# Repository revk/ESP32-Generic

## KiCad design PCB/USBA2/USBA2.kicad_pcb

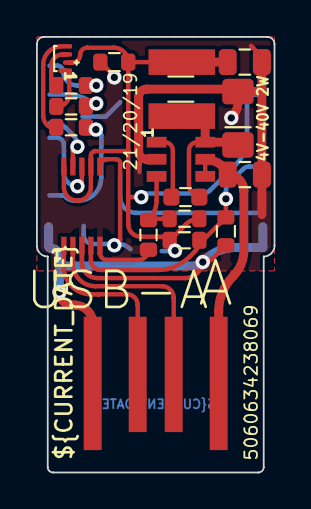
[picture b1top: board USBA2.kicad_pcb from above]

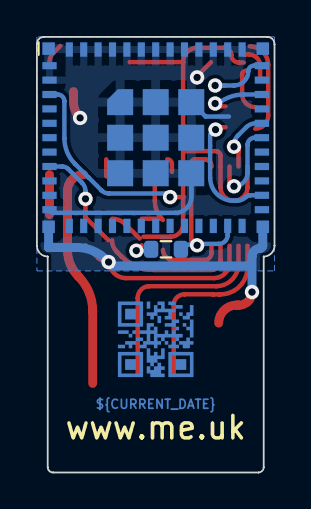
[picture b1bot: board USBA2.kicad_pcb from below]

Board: 2 copper layers, 13.2 x 24.2 mm, 20 parts (3 on the bottom side), 16 nets.

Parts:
C1: 100nF; C_0603_
C2: 2.2uF; C_0805_
C3: 10uF; C_0805_
C4: 100nF; C_0603
C5: 1uF; C_0603
D1: LED_BARG; MHS190RGBCT
D2: Schottky; D_1206_
J1: USB_A; USB-A-PCB
L1: 6.8uH; L_4x4_
R1: 300R; R_0603
R2: 1K; R_0603
R3: 100R; R_0603
R4: 100k 1%; R_0603
R5: 30k 1%; R_0603
R6: 10k; R_0603
R7: 4k7; R_0603
U1: ESP32-PICO-MINI-02
U2: LMR16006YDDCR; SOT-23-Thin-6-Reg
U3: CH340X
U4: QR; QR-GENERIC

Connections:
+3.3V: C4.1, D1.2 (A), R4.1, R6.1, R7.1, U1.3 (3V3), U2.7 (VOUT), U3.7 (VCC), U3.10 (V3)
B: R3.2, U1.33 (IO19)
DC: J1.1 (VBUS), U2.4 (SHDN), U2.5 (VIN)
EN: C5.2, R6.2, U1.8 (EN), U3.4 (~RTS)
G: R2.2, U1.26 (IO20)
GND: C4.2, C5.1, J1.4 (GND), R5.1, U1.1 (GND), U1.2 (GND), U1.11 (GND), U1.14 (GND), U1.36 (GND), U1.37 (GND), U1.38 (GND), U1.39 (GND), U1.40 (GND), U1.41 (GND), U1.42 (GND), U1.43 (GND), U1.44 (GND), U1.45 (GND), U1.46 (GND), U1.47 (GND), U1.48 (GND), U1.49 (GND), U1.50 (GND), U1.51 (GND), U1.52 (GND), U1.53 (GND), U2.2 (GND), U3.3 (GND), U3.5 (~CTS)
GPIO0: R7.2, U1.23 (IO0), U3.6 (TNOW/~DTR)
I: U1.30 (RXD0), U3.8 (TXD)
unnamed: D1.1 (BK), R3.1
unnamed: D1.4 (GK), R2.1
unnamed: D1.3 (RK), R1.1
unnamed: J1.3 (D+), U3.1 (UD+)
unnamed: J1.2 (D-), U3.2 (UD-)
unnamed: R4.2, R5.2, U2.3 (FB)
O: U1.31 (TXD0), U3.9 (RXD)
R: R1.2, U1.35 (IO21)

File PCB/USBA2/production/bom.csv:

Designator,Footprint,Quantity,Value,LCSC Part #
C1,C_0603_,1,100nF,C30926
C2,C_0805_,1,2.2uF,C19110
C3,C_0805_,1,10uF,C17024
C4,C_0603,1,100nF,
C5,C_0603,1,1uF,
D1,MHS190RGBCT,1,LED_BARG,C409798
D2,D_1206_,1,Schottky,C143805
L1,L_4x4_,1,6.8uH,C354575
R1,R_0603,1,300R,
R2,R_0603,1,1K,
R3,R_0603,1,100R,
R4,R_0603,1,100k 1%,C14675
R5,R_0603,1,30k 1%,C100001
R6,R_0603,1,10k,
R7,R_0603,1,4k7,
U1,ESP32-PICO-MINI-02,1,ESP32-PICO-MINI-02,C2980306
U2,SOT-23-Thin-6-Reg,1,LMR16006YDDCR,C290195
U3,CH340X,1,CH340X,C3035748

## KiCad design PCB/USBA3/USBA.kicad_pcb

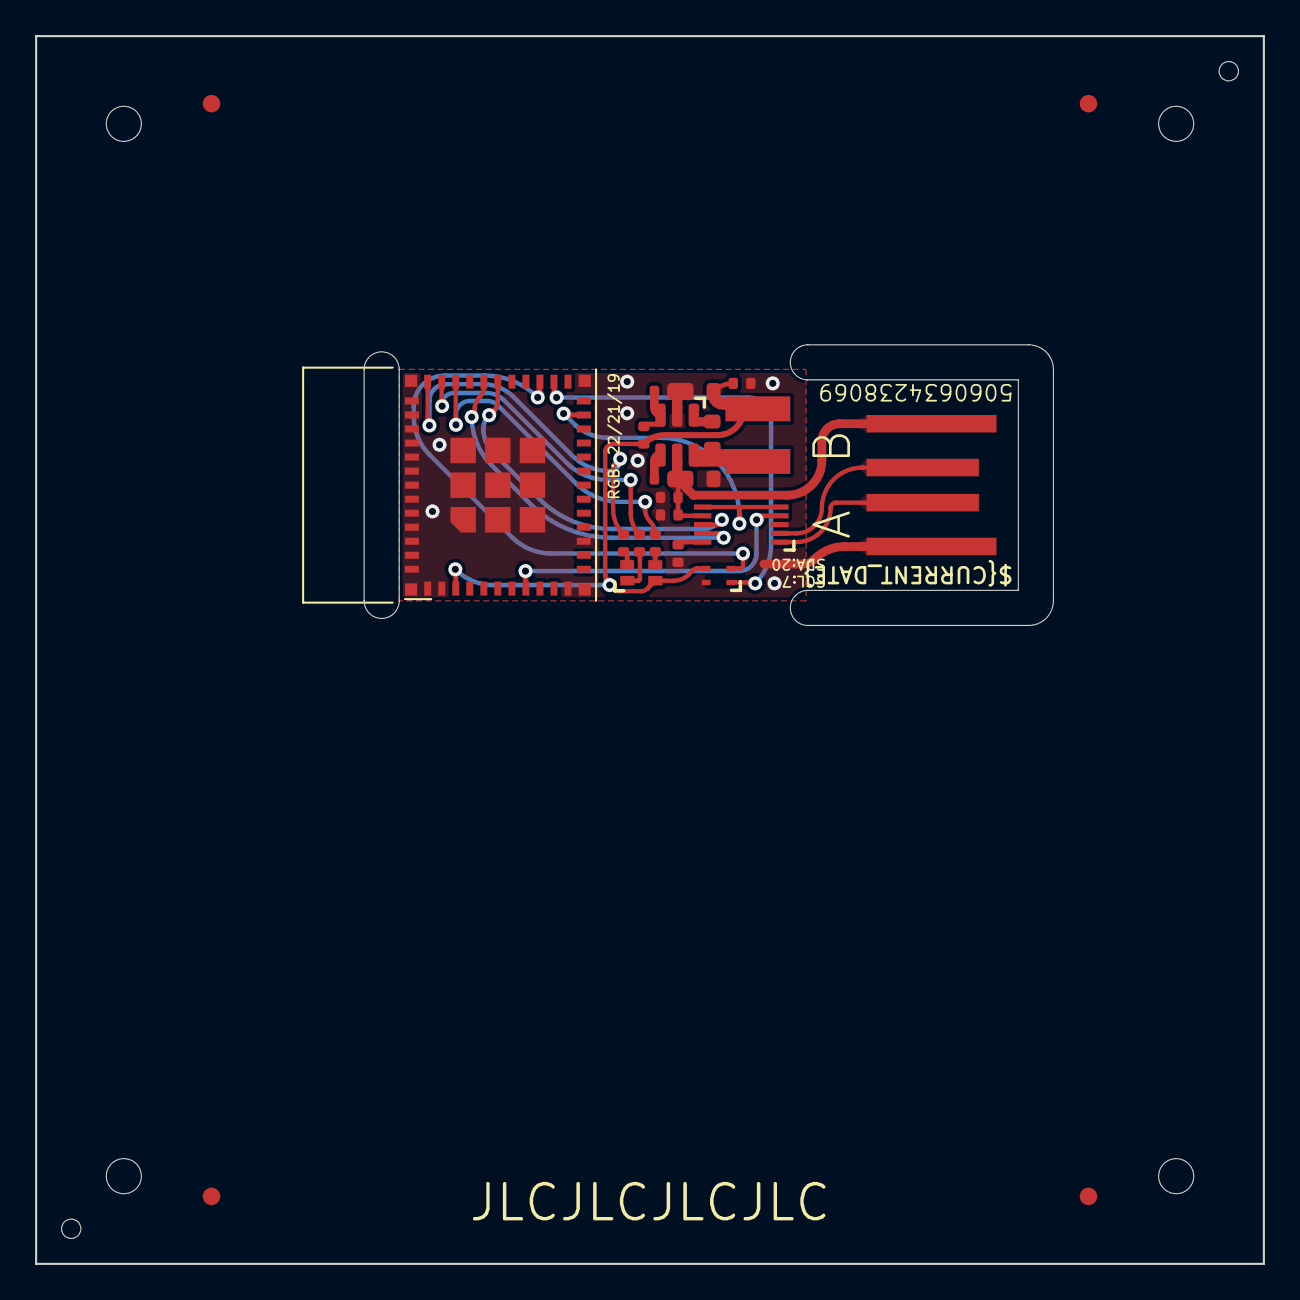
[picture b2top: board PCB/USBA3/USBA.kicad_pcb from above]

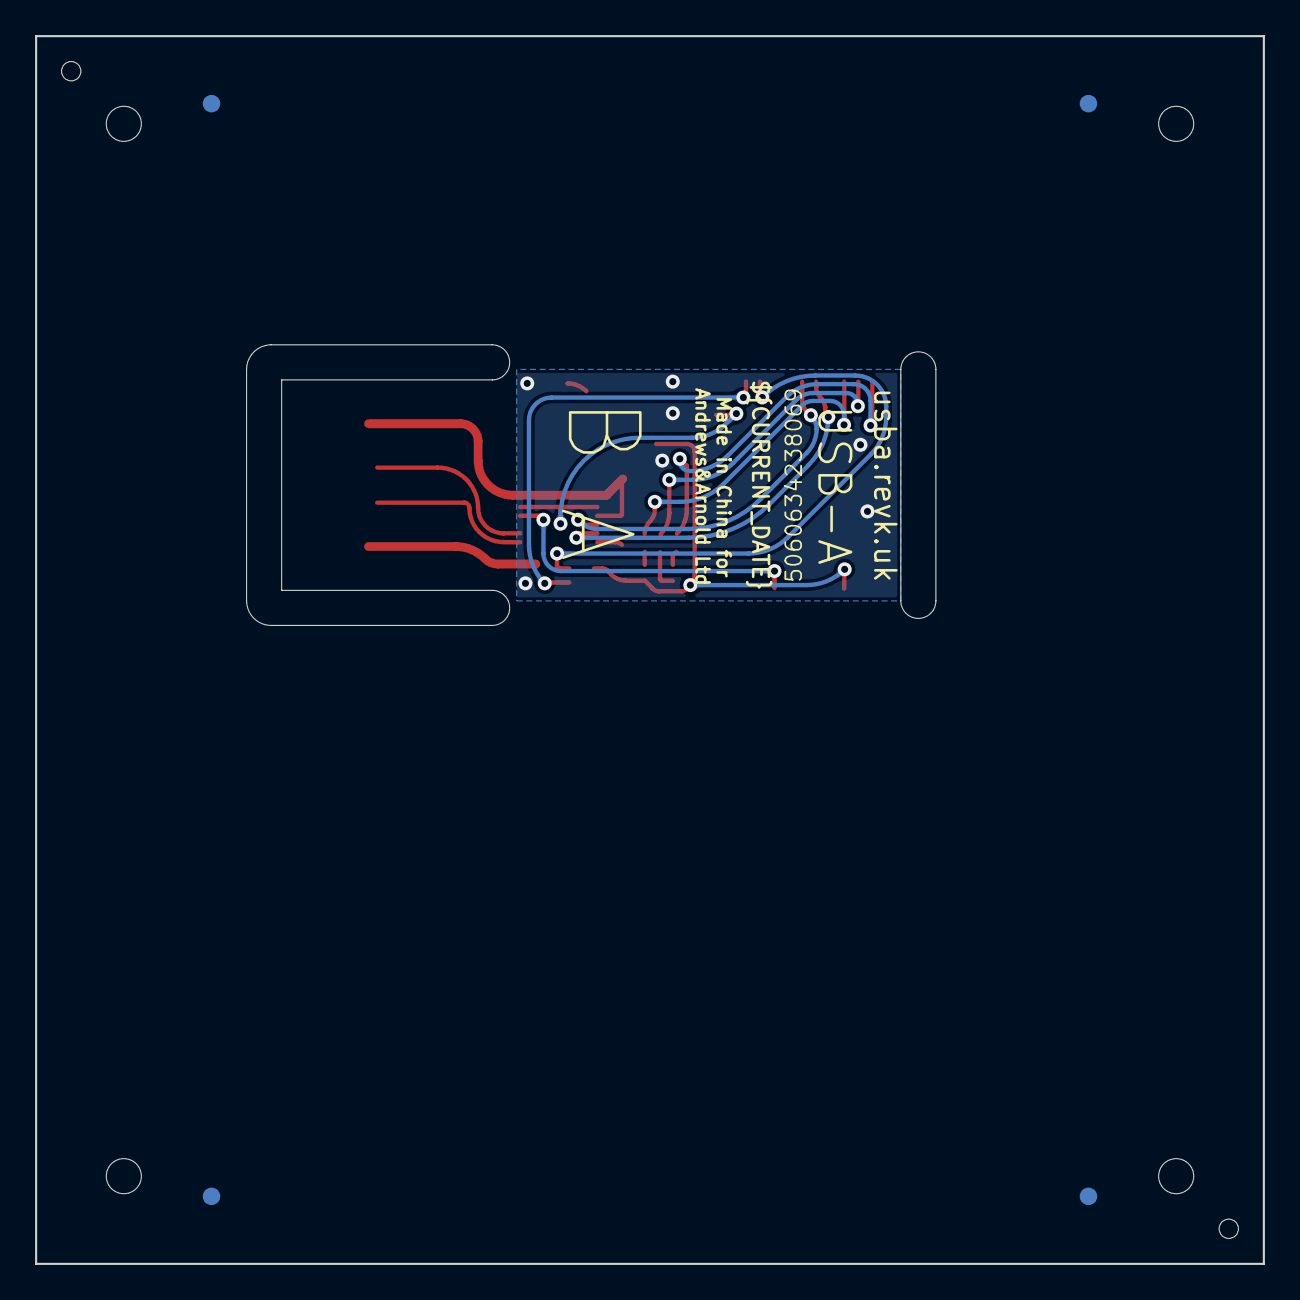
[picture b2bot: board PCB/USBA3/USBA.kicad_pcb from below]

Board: 2 copper layers, 70.0 x 70.0 mm, 23 parts (2 on the bottom side), 18 nets.

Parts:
C1: 22uF; C_0402
C2: 10nF; C_0402
C3, C4: 100nF; C_0402
C6: 10uF 50V; C_0603_
C7: 10uF 6.3V; C_0603_
C8: 100nF; C_0603_
D2: RGB; LED-RGB-1.6x1.6
J1: USB_A; USB-A-PCB
L2: 10uH; L_4x4_
PCB1: 70x70; PCB7070
R4: 680R; R_0402
R5: 2K; R_0402
R7: 220R; R_0402
R9: 124k; R_0402_
R10: 39k2; R_0402_
R11: 1M; R_0402_
U1: ESP32-PICO-MINI-02
U3: CH340X
U5: MD8942; SOT-23-6-MD8942
U6: SHT40; Sensirion_DFN-4_1.5x1.5mm_P0.5mm_SHT4x
V1, V2: 70; VCUT70

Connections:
+3.3V: C4.1, D2.4 (A), U1.3 (3V3), U5.8 (VOUT), U6.3 (VDD)
B: R7.2, U1.33 (IO19)
EN: U1.8 (EN), U3.4 (~RTS)
G: R5.2, U1.35 (IO21)
GND: C1.1, C2.1, C3.1, C4.2, J1.4 (GND), U1.1 (GND), U1.2 (GND), U1.11 (GND), U1.14 (GND), U1.36 (GND), U1.37 (GND), U1.38 (GND), U1.39 (GND), U1.40 (GND), U1.41 (GND), U1.42 (GND), U1.43 (GND), U1.44 (GND), U1.45 (GND), U1.46 (GND), U1.47 (GND), U1.48 (GND), U1.49 (GND), U1.50 (GND), U1.51 (GND), U1.52 (GND), U1.53 (GND), U3.3 (GND), U5.2 (GND), U5.7 (GND), U6.4 (VSS)
GPIO0: U1.23 (IO0), U3.5 (~CTS), U3.6 (TNOW/~DTR)
I: U1.30 (RXD0), U3.8 (TXD)
unnamed: D2.3 (BK), R7.1
unnamed: D2.2 (GK), R5.1
unnamed: D2.1 (RK), R4.1
unnamed: J1.3 (D+), U3.1 (UD+)
unnamed: J1.2 (D-), U3.2 (UD-)
unnamed: C2.2, U3.10 (V3)
O: U1.31 (TXD0), U3.9 (RXD)
R: R4.2, U1.34 (IO22)
SCL: U1.27 (IO7), U6.2 (SCL)
SDA: U1.26 (IO20), U6.1 (SDA)
VBUS: C1.2, C3.2, J1.1 (VBUS), U3.7 (VCC), U5.5 (VIN)

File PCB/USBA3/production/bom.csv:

Designator,Footprint,Quantity,Value,LCSC Part #
C1,C_0402,1,22uF,
C2,C_0402,1,10nF,
"C3, C4",C_0402,2,100nF,
C6,C_0603_,1,10uF 50V,C1591
C7,C_0603_,1,10uF 6.3V,C1691
C8,C_0603_,1,100nF,
D2,LED-RGB-1.6x1.6,1,RGB,C264508
L2,L_4x4_,1,10uH,
R10,R_0402_,1,39k2,
R11,R_0402_,1,1M,
R4,R_0402,1,680R,
R5,R_0402,1,2K,
R7,R_0402,1,220R,
R9,R_0402_,1,124k,
U1,ESP32-PICO-MINI-02,1,ESP32-PICO-MINI-02,C2980306
U3,CH340X,1,CH340X,C3035748
U5,SOT-23-6-MD8942,1,MD8942,C2684786
U6,Sensirion_DFN-4_1.5x1.5mm_P0.5mm_SHT4x,1,SHT40,C2909890

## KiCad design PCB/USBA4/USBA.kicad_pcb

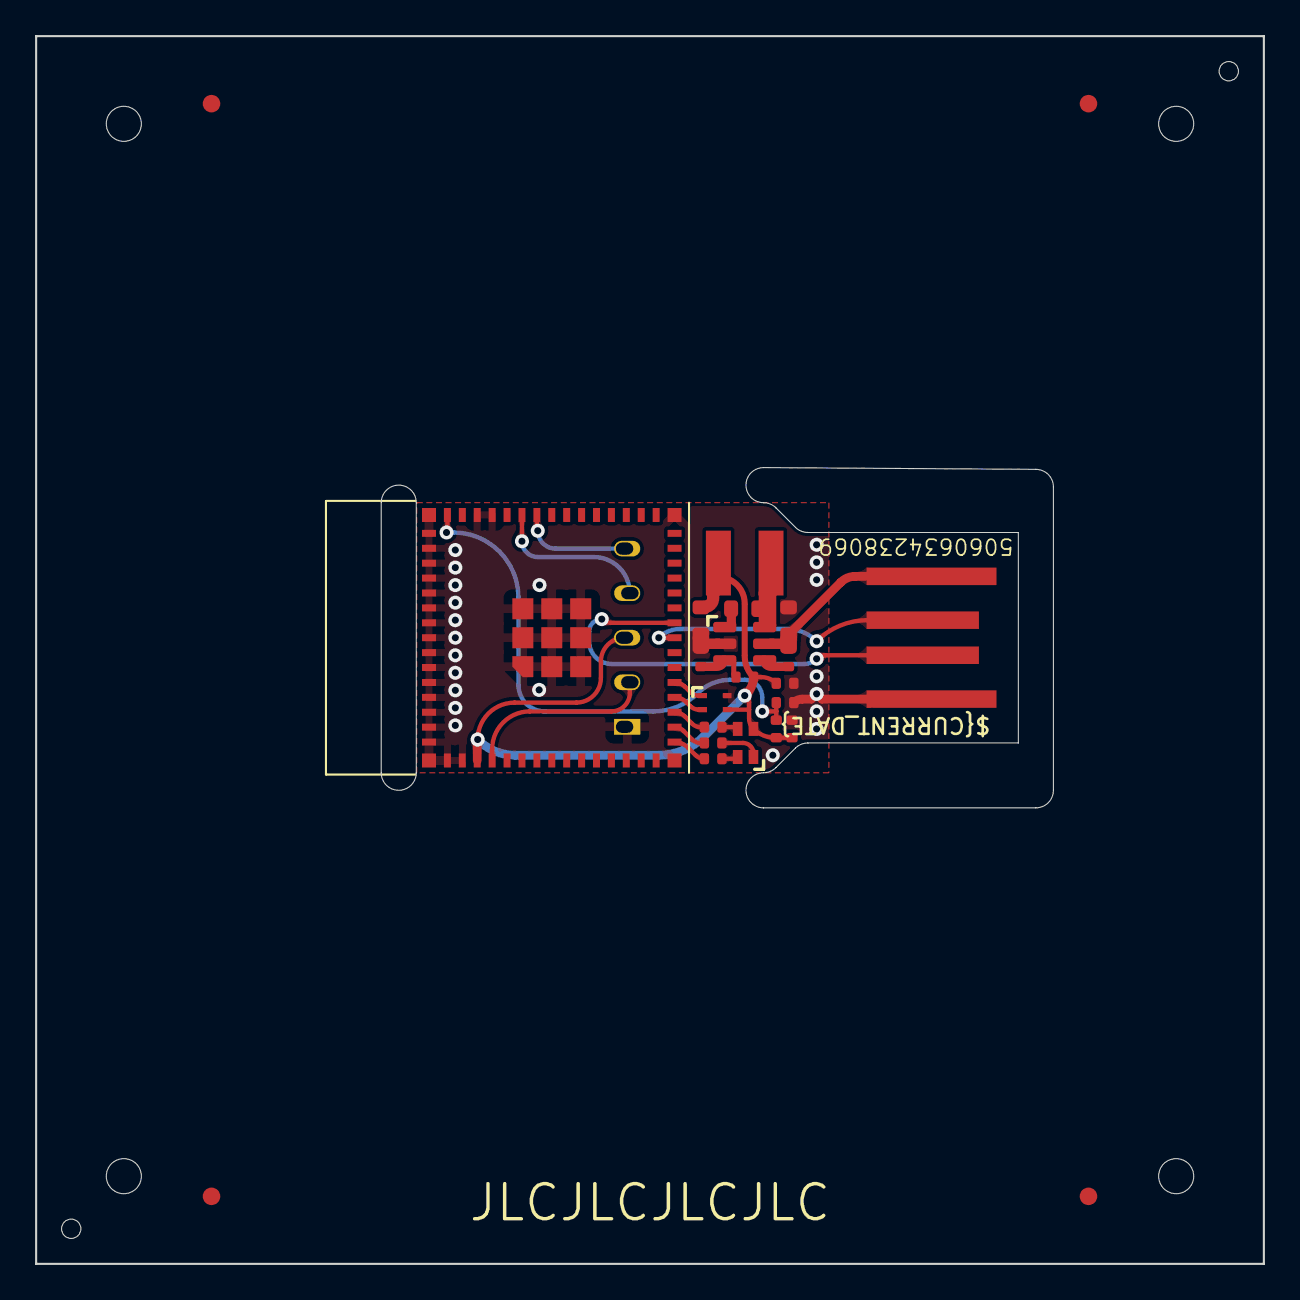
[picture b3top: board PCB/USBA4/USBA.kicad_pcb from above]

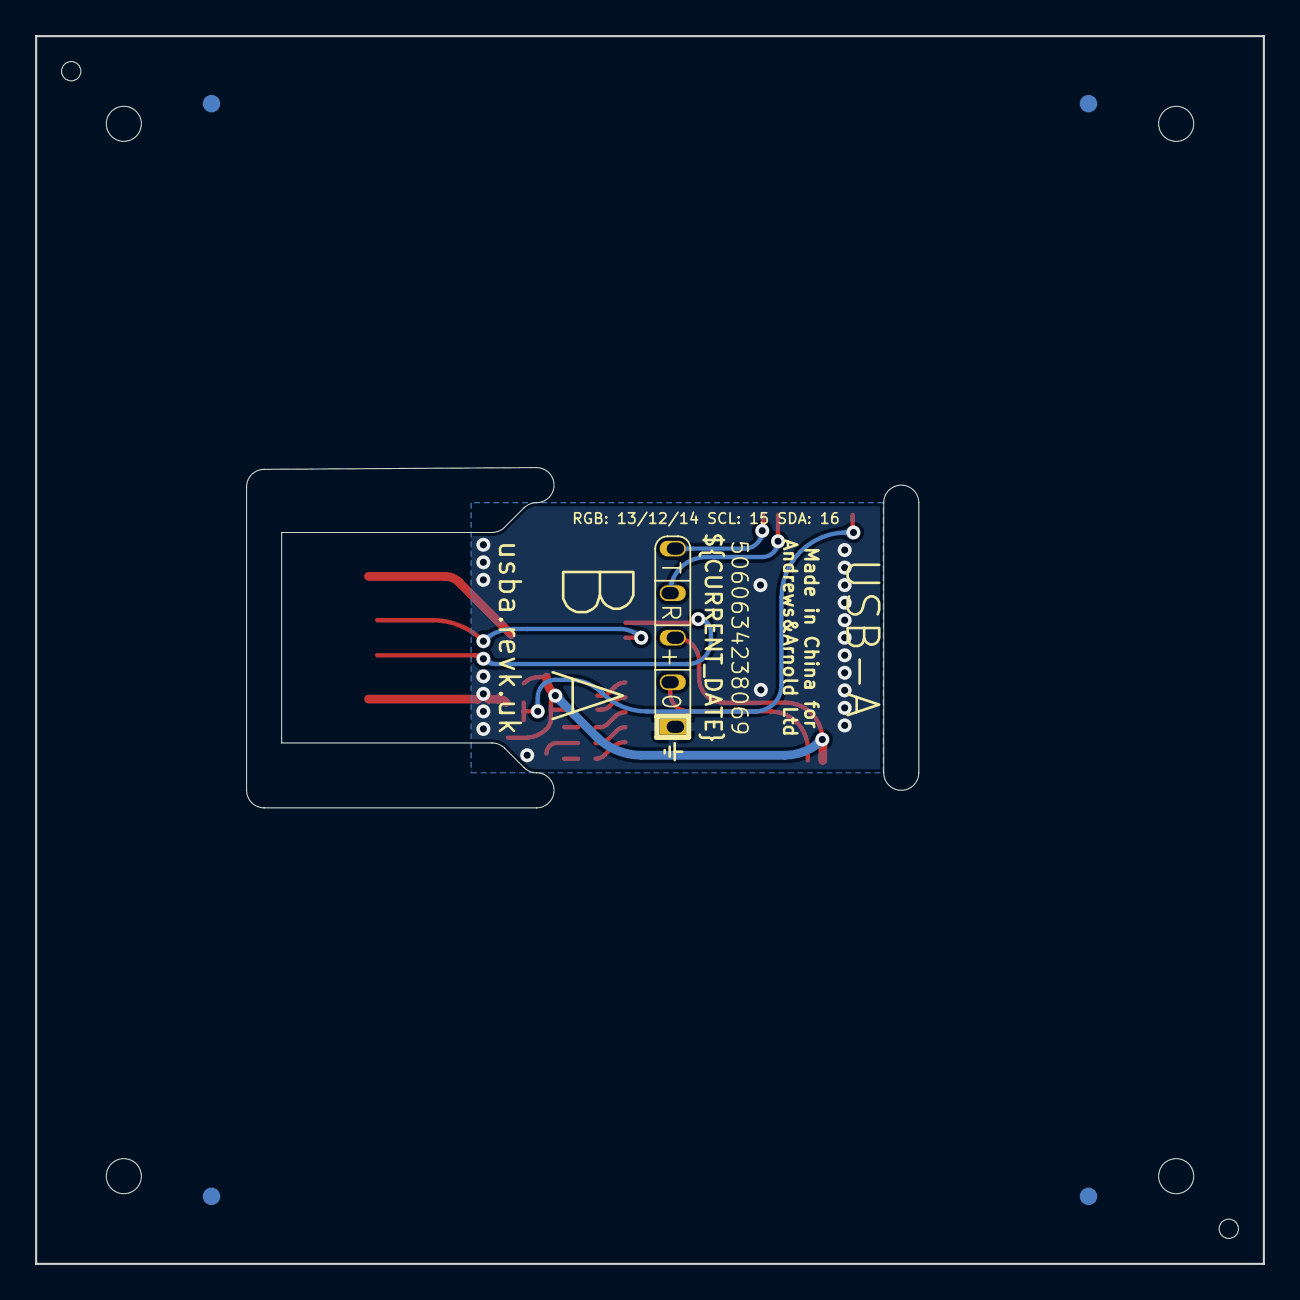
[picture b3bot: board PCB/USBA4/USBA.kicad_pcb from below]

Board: 2 copper layers, 70.0 x 70.0 mm, 23 parts (3 on the bottom side), 17 nets.

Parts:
C1: 100nF; C_0402
C2: 22uF; C_0402
C3: 1uF; C_0402
C6: 10uF 50V; C_0603_
C7: 10uF 6.3V; C_0603_
C8: 100nF; C_0603_
D2: RGB; LED-RGB-1.6x1.6
J1: USB_A; USB-A-PCB
J2: Shelly
L2: 10uH; L_4x4_
PCB1: 70x70; PCB7070
R1: 10K; R_0402
R4: 680R; R_0402
R5: 2K; R_0402
R7: 220R; R_0402
R9: 124k; R_0402_
R10: 39k2; R_0402_
R11: 1M; R_0402_
U2: ESP32-S3-MINI-1
U5: MD8942; SOT-23-6-MD8942
U6: SHT40; Sensirion_DFN-4_1.5x1.5mm_P0.5mm_SHT4x
V1, V2: 70; VCUT70

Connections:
+3.3V: C1.1, C2.1, D2.4 (A), J2.3 (3V3), R1.1, U2.3 (3V3), U5.8 (VOUT), U6.3 (VDD)
B: R7.2, U2.18 (GPIO14)
D+: J1.3 (D+), U2.24 (GPIO20)
D-: J1.2 (D-), U2.23 (GPIO19)
G: R5.2, U2.16 (GPIO12)
GND: C1.2, C2.2, C3.2, J1.4 (GND), J2.1 (GND), U2.1 (GND), U2.2 (GND), U2.42 (GND), U2.43 (GND), U2.46 (GND), U2.47 (GND), U2.48 (GND), U2.49 (GND), U2.50 (GND), U2.51 (GND), U2.52 (GND), U2.53 (GND), U2.54 (GND), U2.55 (GND), U2.56 (GND), U2.57 (GND), U2.58 (GND), U2.59 (GND), U2.60 (GND), U2.61 (GND), U2.62 (GND), U2.63 (GND), U2.64 (GND), U2.65 (GND), U5.2 (GND), U5.7 (GND), U6.4 (VSS)
unnamed: D2.3 (BK), R7.1
unnamed: D2.2 (GK), R5.1
unnamed: D2.1 (RK), R4.1
unnamed: J2.2 (0), U2.4 (GPIO0)
unnamed: J2.4 (Rx), U2.40 (GPIO44)
unnamed: J2.5 (Tx), U2.39 (GPIO43)
unnamed: C3.1, R1.2, U2.45 (EN)
R: R4.2, U2.17 (GPIO13)
SCL: U2.19 (GPIO15), U6.2 (SCL)
SDA: U2.20 (GPIO16), U6.1 (SDA)
VBUS: J1.1 (VBUS), U5.5 (VIN)

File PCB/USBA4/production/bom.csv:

Designator,Footprint,Quantity,Value,LCSC Part #
C1,C_0402,1,100nF,
C2,C_0402,1,22uF,
C3,C_0402,1,1uF,
C6,C_0603_,1,10uF 50V,C1591
C7,C_0603_,1,10uF 6.3V,C1691
C8,C_0603_,1,100nF,
D2,LED-RGB-1.6x1.6,1,RGB,C264508
L2,L_4x4_,1,10uH,
R1,R_0402,1,10K,
R10,R_0402_,1,39k2,
R11,R_0402_,1,1M,
R4,R_0402,1,680R,
R5,R_0402,1,2K,
R7,R_0402,1,220R,
R9,R_0402_,1,124k,
U2,ESP32-S3-MINI-1,1,ESP32-S3-MINI-1,C3013941
U5,SOT-23-6-MD8942,1,MD8942,C2684786
U6,Sensirion_DFN-4_1.5x1.5mm_P0.5mm_SHT4x,1,SHT40,C2909890
